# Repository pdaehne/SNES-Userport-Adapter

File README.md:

# SNES Controller to CBM Userport Adapter

This repository contains the KiCad project and Gerber files for an adapter that
allows to connect a SNES controller to the Userport of many Commodore 8-bit
computers like the C64, C128, PET, Plus/4 and VIC-20.

This adapter was developed for the game
"[PETSCII Robots](https://www.the8bitguy.com/category/the-8-bit-guy/petscii-robots/)"
by The 8-bit Guy. The official adapter is available for purchase from
[Texelec](https://texelec.com/product/snes-adapter-commodore/). When you live
in North America, I recommend that you buy it there instead of using this
clone. This repository is only for persons living in countries where shipping
from North America and taxes are prohibitively expensive.

The Adapter is also supported by some other games. See the Texelec web site for
more information. You can also use the C64 program
[Joyride](https://github.com/T-Pau/Joyride) to test the adapter.

> [!WARNING]
> This adapter works reliable with original SNES controllers, but it does not
> work with certain third-party/aftermarket controllers! See the section
> "[When your controller does not work](#when-your-controller-does-not-work)"
> below for more information. Use this adapter at your own risk!

## Ordering the PCB

The subdirectory "gerber-files" contains a Zip file you can use to order the PCB
from PCB manufacturers like PCBWay or JLCPCB. Simply upload the Zip on their web
page. I recommend to order the standard PCB thickness of 1.6mm and HASL
finishing.

## Building the Adapter

### Bill of Materials

* __1x SNES Controller Socket Right Angle__.

  Search for "90 degree female 7 Pin SNES socket" on AliExpress.

* __1x 24 Pin Edge Connector 3.96mm pitch__.

  Search for "24 Pin Edge Connector 3.96mm" on AliExpress. There are two
  types of connectors, one with pins, and one with soldering lugs. They
  both work, but I recommend the ones with pins.

* (Optional) __1x 3x1 Male Pin Header Through Hole Right Angle 2.54mm pitch__.

  This is only needed when you want to build the external power supply for PETs
  without 5V on the Userport.

* (Optional) __1x Jumper 2.54mm pitch__.

  Also for the external power supply.

* (Optional) __1x 50-500 Ohm Resistor Through Hole 0207 size__.

  This is only needed when using the adapter on an old PET that does not have
  a speaker. In that case, you can fit the adapter with an audio jack for
  sound output.

* (Optional) __1x 3.5mm Audio Jack__ (Ledino KB 3 SPRS or Shenzhen Intech
  PJ-324)

  Also for sound output on old PETs.

### Soldering the Power Supply

The first PET computers do not have +5V on pin 2 of the Userport. For that
reason, the adapter supports a connector for an external power supply.

When you do not plan to use the adapter on such a PET, you can simply close
the jumper on the bottom of the PCB with a blob of solder. This will supply
the SNES controller with +5V from pin 2 of the Userport.

When you want to use the option to use an external power supply, you can solder
the 3x1 male pin header on the top side of the PCB. To use the +5V provided by
pin 2 of the Userport, simply put a jumper on pins 1 and 2 of the pin header.
To use an external power supply, connect +5V to pin 2 and ground to pin 3 by
using female Dupont connectors. You can also use the tape port as an external power
supply, simply connect pin 2 or B of the tape port to pin 2 of the pin header
(no need to connect ground in this case).

### Soldering the Audio Interface

The first PETs did not have any sound output. A popular workaround is to connect
active speakers to pin M of the Userport (search for "PET CB2 sound" on the
Internet). This is also supported by the adapter. Simply solder a resistor
(50-500 Ohms) and an audio jack to the PCB. This of course is not needed on
other Commodore machines and completely optional. It is also currently untested,
so please drop me note when you successfully use this option on a PET.

Unfortunately, getting the audio jack into the PCB is extremly fiddly. Even
though it is an official KiCad footprint, the holes seem to be a little bit to
small.

### Soldering the Userport Edge Connector

Before soldering the Userport connector, you have to bend the pins a little bit
inwards so that they touch the surface of the PCB. Carefully push down the
connector on a hard surface to bend the pins uniformly on both sides.

When you are satisfied with the result, slide the connector onto the PCB. Doing
that can be a little bit fiddly, be careful not to bend any pins sideways!

Solder the edge connector into place. You'll need a lot of solder and heat.

### Soldering the SNES Controller Socket

When you order your SNES controller socket, you'll probably get a socket where
the pins point in the wrong direction. That is not a problem, the pins are only
sticked into the socket and can be rotated into the other direction. By using a
pair of pliers, carefully pull out the pins a little bit, rotate them by 180
degrees, and push them back.

Solder the socket into place. You'll need a lot of heat, especially for the
ground pin (that's the outermost pin on the round side).

## 3D-Printing a Case

In the subdirectory "[case](case)" of this repository there are STL files you
can use to print a case for the adapter on your 3D printer. You need a
self-tapping flat-headed M3 Phillips screw. Mine had a length of 12mm, but any
length between 10mm and 16mm should work.

There are two variants of the case, one for the PET version with holes for the
power supply and the audio connector, and one closed version in case you
did not populate the PET-specific parts of the PCB.

## Using the Adapter in your Software

The SNES controller actually just consists of a 16-bit shift register (two
8-bit shift registers on older versions). The 12 buttons are connected to the
parallel inputs of the shift register, and their state gets serially transmitted
to the computer. There are two lines from the computer to the controller called
"Latch" and "Clock", and one line from the controller to the computer called
"Data". When the computer toggles "Latch", the shift register copies the state
of the 12 buttons into its internal register. When the computer toggles "Clock",
the shift register sends the contents of its internal register serially over
"Data" to the computer. The first 12 bits correspond to the 12 buttons, and the
last 4 bits are unused. Even though it might be tempting to ignore the last
4 bits and save some time, I strongly recommend to read the full 16 bits,
otherwise your software might not work with certain third-party controllers.
See the section
"[When your controller does not work](#when-your-controller-does-not-work)"
below for more information.

There is a small example assembler programm called
[snes_userport.asm](snes_userport.asm) in this repository which demonstrates
how to correctly read the SNES controller on PET, VIC-20, Plus/4, C64 and C128
machines. Use [64tass](https://sourceforge.net/projects/tass64/) to compile the
example, the command lines for the different target systems are documented at
the top of the source code. Feel free to integrate this example code into your
own software!

There is a nice [blog post by Michael Steil](https://www.pagetable.com/?p=1365)
that explains how the SNES controller works more in detail. He also provides a
software example, but keep in mind that he is using different pins of the
Userport, so you have to adjust his example when using it with this adapter.

The
[source code of PETSCII Robots](https://github.com/zeropolis79/PETSCIIRobots-C64/blob/main/C64ROBOTS.ASM)
is also available on Github. Search for the subroutine called
"SNES_CONTROLER_READ" to see how The 8-bit Guy reads the button states. But keep
in mind that PETSCII Robots incorrectly only reads 12 bits from the SNES
controller, which does not work with certain third-party/after-market
controllers.

Finally, there is the
[source code of Joyride](https://github.com/T-Pau/Joyride/blob/master/src/petscii.s)
available on Github. Starting with version 1.7, Joyride correctly reads the
full 16 bits from the SNES controller.

## When your controller does not work

This adapter works reliable with original SNES controllers, but there are
certain third-party/aftermarket controllers which do not work. Investigation
revealed that this is not an issue with the adapter, but with the controllers.
These controllers do not behave correctly, they do not work when software does
not read the full 16 bits from the shift register, but only the first 12 bits
which are actually needed to cover all buttons of the SNES controller. You can
check if your controller is also affected by this problem by using the free
joystick test program [Joyride](https://github.com/T-Pau/Joyride). Starting
with version 1.7, Joyride reads the full 16 bits, so it should work correctly
with all controllers out there.

Unfortunately most software using the SNES Userport adapter incorrectly reads
only 12 bits, most prominently PETSCII Robots itself. It is easy to fix this
problem, but this has to be done by the respective software developers. Since
the source code of PETSCII Robots is available, I have prepared patched versions
for all systems in the folder [PETSCIIRobots-patched](PETSCIIRobots-patched) of
this repository:

* __[c64robots.v1.2](PETSCIIRobots-patched/c64robots.v1.2)__: Patched C64
  version (v1.2). Replace the file "c64robots" in the disk image with this
  file.
* __[c64robots.v1.3](PETSCIIRobots-patched/c64robots.v1.3)__: Patched C64
  version (v1.3). Replace the file "c64robots" in the disk image with this
  file.
* __[game-64x](PETSCIIRobots-patched/game-64x)__: Patched C64 REU
  version. Replace the file "game-64x" in the disk image with this
  file.
* __[common-128](PETSCIIRobots-patched/common-128)__: Patched C128
  version. Replace the file "common-128" in the disk image with this
  file.
* __[plus4gfx](PETSCIIRobots-patched/plus4gfx)__: Patched Plus/4
  version. Replace the file "plus4gfx" in the disk image with this
  file.
* __[vicrobots](PETSCIIRobots-patched/vicrobots)__: Patched VIC-20
  version. Replace the file "vicrobots" in the disk image with this
  file.
* __[petrobots](PETSCIIRobots-patched/petrobots)__: Patched PET
  version. Replace the file "petrobots" in the disk image with this
  file.
* __[petrobots.gfx](PETSCIIRobots-patched/petrobots.gfx)__: Patched PET
  version with custom character set. Replace the file "petrobots" in the disk
  image with this file.

Please keep in mind that most of these patched versions are untested, so use
at your own risk!

## License

SNES Controller to CBM Userport Adapter (c) by Patrick Dähne

SNES Controller to CBM Userport Adapter is licensed under a
Creative Commons Attribution-NonCommercial-ShareAlike 4.0 International License.

You should have received a copy of the license along with this
work. If not, see <https://creativecommons.org/licenses/by-nc-sa/4.0/>.

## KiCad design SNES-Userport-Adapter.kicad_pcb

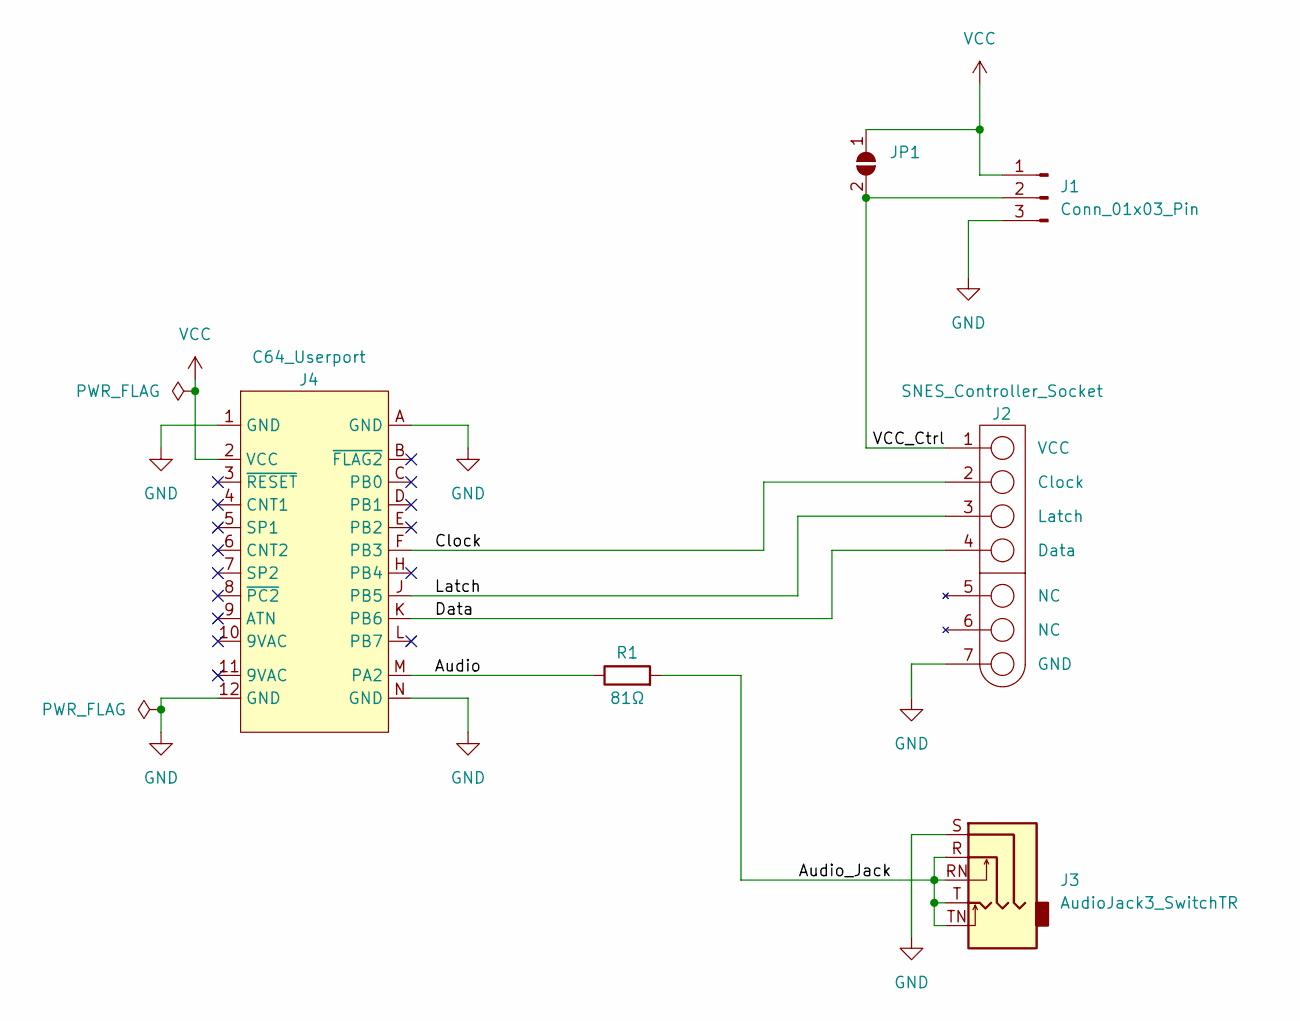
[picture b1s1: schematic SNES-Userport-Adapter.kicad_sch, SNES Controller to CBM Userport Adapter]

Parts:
J1: Conn_01x03_Pin; PinHeader_1x03_P2.54mm_Horizontal
J2: SNES_Controller_Socket
J3: AudioJack3_SwitchTR; Jack_3.5mm_Ledino_KB3SPRS_Horizontal
J4: C64_Userport
JP1: SolderJumper_2_Open; SolderJumper-2_P1.3mm_Open_RoundedPad1.0x1.5mm
R1: 81Ω; R_Axial_DIN0207_L6.3mm_D2.5mm_P10.16mm_Horizontal

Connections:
/Audio: J4.M (PA2), R1.1
/Audio_Jack: J3.R, J3.RN, J3.T, J3.TN, R1.2
/Clock: J2.2 (Clock), J4.F (PB3)
/Data: J2.4 (Data), J4.K (PB6)
/Latch: J2.3 (Latch), J4.J (PB5)
/VCC_Ctrl: J1.2, J2.1 (VCC), JP1.2 (B)
GND: J1.3, J2.7 (GND), J3.S, J4.1 (GND), J4.12 (GND), J4.A (GND), J4.N (GND)
VCC: J1.1, J4.2 (VCC), JP1.1 (A)

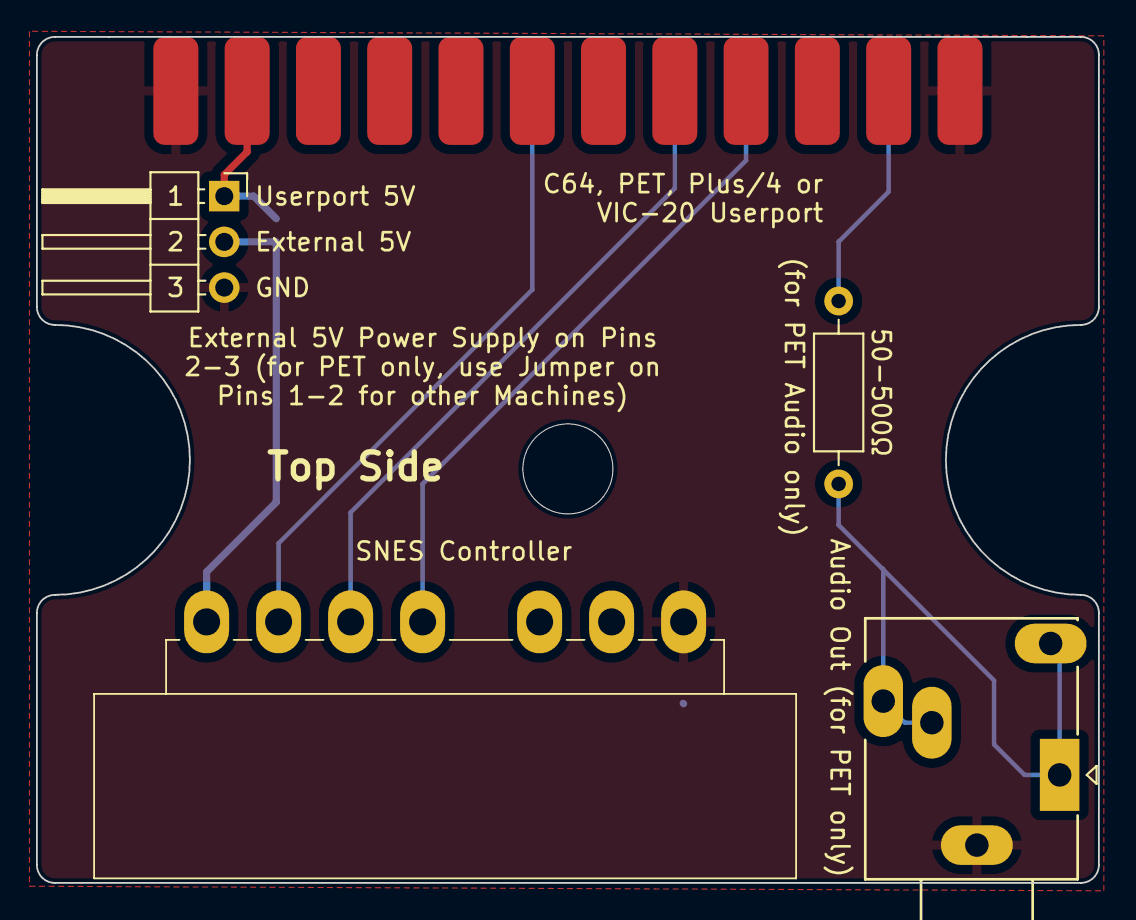
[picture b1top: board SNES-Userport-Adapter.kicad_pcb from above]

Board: 2 copper layers, 59.0 x 47.0 mm, 6 parts (1 on the bottom side), 8 nets.

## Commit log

2023-11-25 Initial check-in
2023-11-25 Renamed license file
2023-11-25 Added gerber files
2023-12-12 Wrote documentation
2023-12-13 Link to raw images
2023-12-22 Added example program
2023-12-23 Some third-party controllers require that we read the full 16 bits to work correctly
2024-08-25 Added some more information about non-working controllers as well as patched versions of PETSCII Robots
2025-01-20 Fixed access rights
2025-12-03 Added recommendation for PCB thickness and finishing
2026-05-18 Added case

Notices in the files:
SNES-Userport-Adapter.kicad_pcb:
Patrick Dähne CC BY-NC-SA 4.0
CC BY-NC-SA 4.0
